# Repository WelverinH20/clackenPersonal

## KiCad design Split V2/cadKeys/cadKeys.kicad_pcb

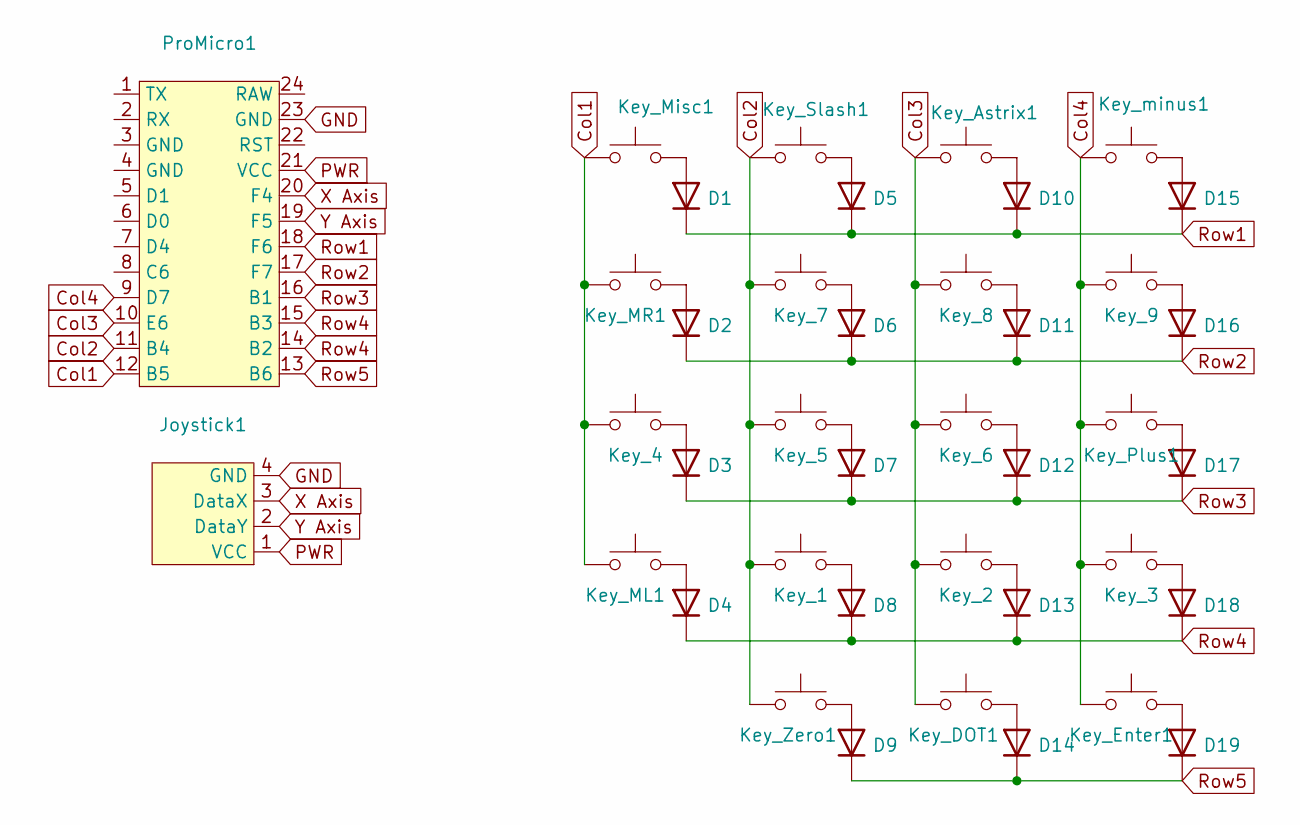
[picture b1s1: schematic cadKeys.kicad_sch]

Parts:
D1, D2, D3, D4, D5, D6, D7, D8, D9, D10, D11, D12, D13, D14, D15, D16, D17, D18, D19: D; D_SOD-123
Joystick1: joystick
Key_1, Key_2, Key_3, Key_4, Key_5, Key_6, Key_7, Key_8, Key_9: SW_Push; SW_Hotswap_Kailh_Choc_V1V2_1.00u
Key_Astrix1: SW_Push; SW_Hotswap_Kailh_Choc_V1V2_1.00u
Key_DOT1: SW_Push; SW_Hotswap_Kailh_Choc_V1V2_1.00u
Key_Enter1: SW_Push; SW_Hotswap_Kailh_Choc_V1V2_2.00u
Key_ML1: SW_Push; SW_Hotswap_Kailh_Choc_V1V2_1.00u
Key_MR1: SW_Push; SW_Hotswap_Kailh_Choc_V1V2_1.00u
Key_Misc1: SW_Push; SW_Hotswap_Kailh_Choc_V1V2_1.00u
Key_Plus1: SW_Push; SW_Hotswap_Kailh_Choc_V1V2_2.00u
Key_Slash1: SW_Push; SW_Hotswap_Kailh_Choc_V1V2_1.00u
Key_Zero1: SW_Push; SW_Hotswap_Kailh_Choc_V1V2_2.00u
Key_minus1: SW_Push; SW_Hotswap_Kailh_Choc_V1V2_1.00u
ProMicro1: ARDUINO_PRO_MICRO

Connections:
Col1: Key_4.1, Key_ML1.1, Key_MR1.1, Key_Misc1.1, ProMicro1.12 (B5)
Col2: Key_1.1, Key_5.1, Key_7.1, Key_Slash1.1, Key_Zero1.1, ProMicro1.11 (B4)
Col3: Key_2.1, Key_6.1, Key_8.1, Key_Astrix1.1, Key_DOT1.1, ProMicro1.10 (E6)
Col4: Key_3.1, Key_9.1, Key_Enter1.1, Key_Plus1.1, Key_minus1.1, ProMicro1.9 (D7)
GND: Joystick1.4 (GND), ProMicro1.23 (GND)
unnamed: D1.2 (A), Key_Misc1.2
unnamed: D2.2 (A), Key_MR1.2
unnamed: D3.2 (A), Key_4.2
unnamed: D4.2 (A), Key_ML1.2
unnamed: D5.2 (A), Key_Slash1.2
unnamed: D6.2 (A), Key_7.2
unnamed: D7.2 (A), Key_5.2
unnamed: D8.2 (A), Key_1.2
unnamed: D9.2 (A), Key_Zero1.2
unnamed: D10.2 (A), Key_Astrix1.2
unnamed: D11.2 (A), Key_8.2
unnamed: D12.2 (A), Key_6.2
unnamed: D13.2 (A), Key_2.2
unnamed: D14.2 (A), Key_DOT1.2
unnamed: D15.2 (A), Key_minus1.2
unnamed: D16.2 (A), Key_9.2
unnamed: D17.2 (A), Key_Plus1.2
unnamed: D18.2 (A), Key_3.2
unnamed: D19.2 (A), Key_Enter1.2
PWR: Joystick1.1 (VCC), ProMicro1.21 (VCC)
Row1: D1.1 (K), D5.1 (K), D10.1 (K), D15.1 (K), ProMicro1.18 (F6)
Row2: D2.1 (K), D6.1 (K), D11.1 (K), D16.1 (K), ProMicro1.17 (F7)
Row3: D3.1 (K), D7.1 (K), D12.1 (K), D17.1 (K), ProMicro1.16 (B1)
Row4: D4.1 (K), D8.1 (K), D13.1 (K), D18.1 (K), ProMicro1.14 (B2), ProMicro1.15 (B3)
Row5: D9.1 (K), D14.1 (K), D19.1 (K), ProMicro1.13 (B6)
X Axis: Joystick1.3 (DataX), ProMicro1.20 (F4)
Y Axis: Joystick1.2 (DataY), ProMicro1.19 (F5)

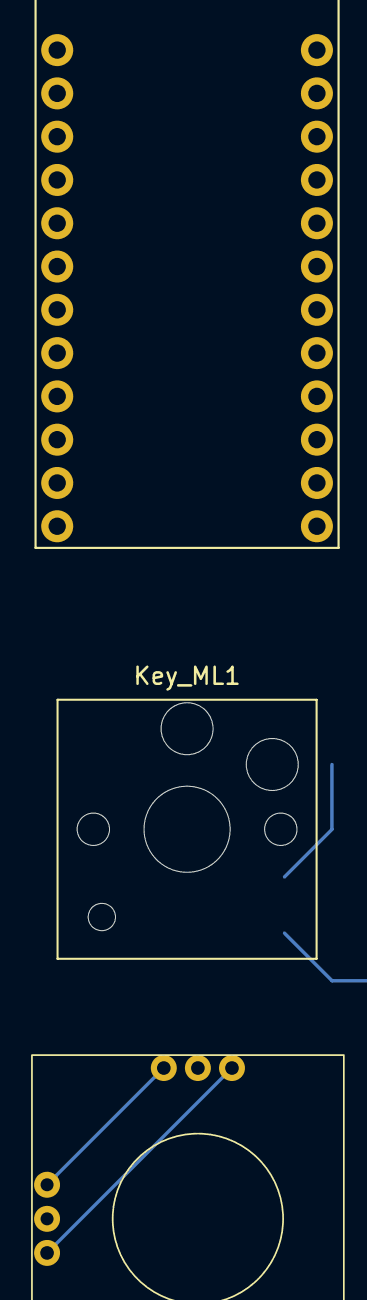
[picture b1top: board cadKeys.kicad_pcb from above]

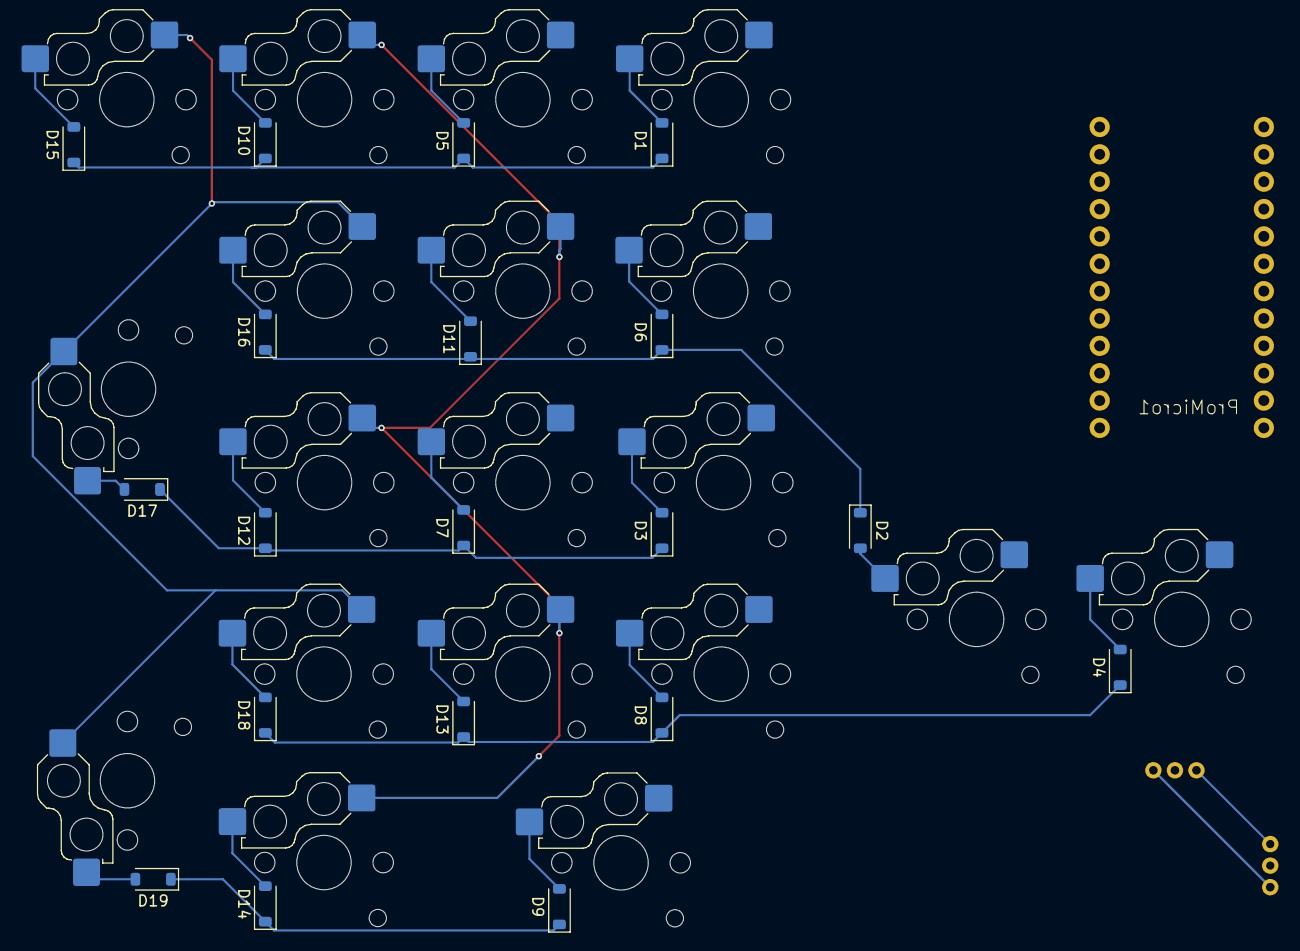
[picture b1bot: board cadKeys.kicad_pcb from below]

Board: 2 copper layers, 40 parts (19 on the bottom side), 32 nets.

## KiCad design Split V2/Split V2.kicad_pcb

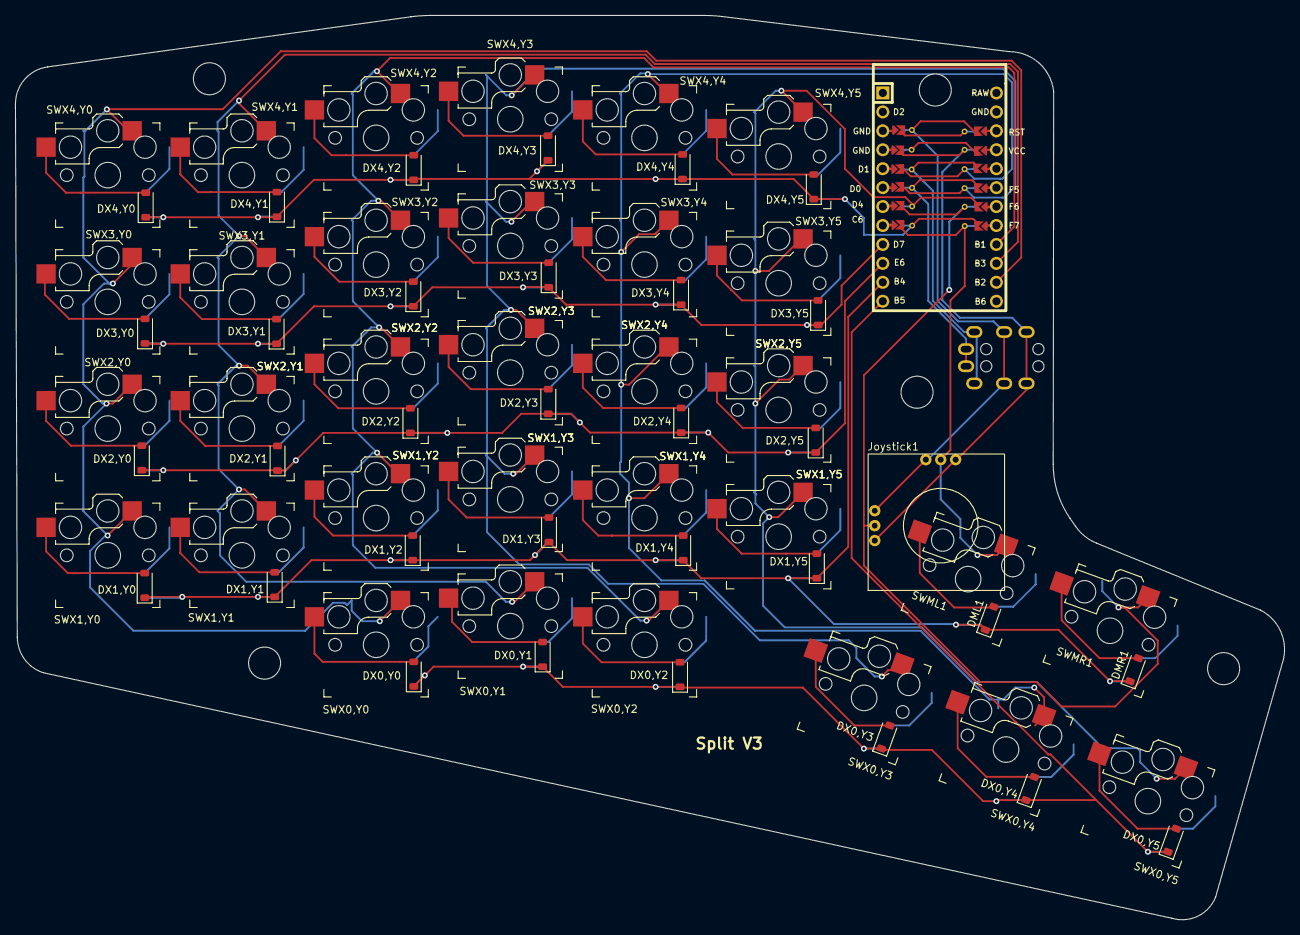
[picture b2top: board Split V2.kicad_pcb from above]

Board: 2 copper layers, 170.2 x 121.3 mm, 67 parts (0 on the bottom side), 49 nets.

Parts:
DML1: D_SOD-123_bothside
DMR1: D_SOD-123_bothside
DX0,Y0, DX0,Y1, DX0,Y2, DX0,Y3, DX0,Y4, DX0,Y5, DX1,Y0, DX1,Y1, DX1,Y2, DX1,Y3, DX1,Y4, DX1,Y5, DX2,Y0, DX2,Y1, DX2,Y2, DX2,Y3, DX2,Y4, DX2,Y5, DX3,Y0, DX3,Y1, DX3,Y2, DX3,Y3, DX3,Y4, DX3,Y5, DX4,Y0, DX4,Y1, DX4,Y2, DX4,Y3, DX4,Y4, DX4,Y5: D_SOD-123_bothside
J1: AudioJack4; TRRS-PJ-320A-dual
Joystick1: joystick
ProMicro1: ArduinoProMicro
SWML1: Kailh_socket_PG1350_optional_reversible
SWMR1: Kailh_socket_PG1350_optional_reversible
SWX0,Y0, SWX0,Y1, SWX0,Y2, SWX0,Y3, SWX0,Y4, SWX0,Y5, SWX1,Y0, SWX1,Y1, SWX1,Y2, SWX1,Y3, SWX1,Y4, SWX1,Y5, SWX2,Y0, SWX2,Y1, SWX2,Y2, SWX2,Y3, SWX2,Y4, SWX2,Y5, SWX3,Y0, SWX3,Y1, SWX3,Y2, SWX3,Y3, SWX3,Y4, SWX3,Y5, SWX4,Y0, SWX4,Y1, SWX4,Y2, SWX4,Y3, SWX4,Y4, SWX4,Y5: Kailh_socket_PG1350_optional_reversible

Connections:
/Net-(DX0,Y3-A): DML1.2 (A), SWML1.2
/Net-(DX0,Y4-A): DMR1.2 (A), SWMR1.2
Col0: ProMicro1.14 (B2), SWX0,Y0.1, SWX1,Y0.1, SWX2,Y0.1, SWX3,Y0.1, SWX4,Y0.1
Col1: ProMicro1.15 (B3), SWX0,Y1.1, SWX1,Y1.1, SWX2,Y1.1, SWX3,Y1.1, SWX4,Y1.1
Col2: ProMicro1.16 (B1), SWX0,Y2.1, SWX1,Y2.1, SWX2,Y2.1, SWX3,Y2.1, SWX4,Y2.1
Col3: ProMicro1.19 (F5), SWX0,Y3.1, SWX1,Y3.1, SWX2,Y3.1, SWX3,Y3.1, SWX4,Y3.1
Col4: ProMicro1.20 (F4), SWX0,Y4.1, SWX1,Y4.1, SWX2,Y4.1, SWX3,Y4.1, SWX4,Y4.1
Col5: ProMicro1.7 (D4), SWX0,Y5.1, SWX1,Y5.1, SWX2,Y5.1, SWX3,Y5.1, SWX4,Y5.1
Gnd: J1.3, Joystick1.4 (GND), ProMicro1.3 (GND)
Joy1: Joystick1.2 (DataY), ProMicro1.18 (F6), SWMR1.1
Joy2: Joystick1.3 (DataX), ProMicro1.17 (F7), SWML1.1
unnamed: DX0,Y0.2 (A), SWX0,Y0.2
unnamed: DX0,Y1.2 (A), SWX0,Y1.2
unnamed: DX0,Y2.2 (A), SWX0,Y2.2
unnamed: DX0,Y3.2 (A), SWX0,Y3.2
unnamed: DX0,Y4.2 (A), SWX0,Y4.2
unnamed: DX0,Y5.2 (A), SWX0,Y5.2
unnamed: DX1,Y0.2 (A), SWX1,Y0.2
unnamed: DX1,Y1.2 (A), SWX1,Y1.2
unnamed: DX1,Y2.2 (A), SWX1,Y2.2
unnamed: DX1,Y3.2 (A), SWX1,Y3.2
unnamed: DX1,Y4.2 (A), SWX1,Y4.2
unnamed: DX1,Y5.2 (A), SWX1,Y5.2
unnamed: DX2,Y0.2 (A), SWX2,Y0.2
unnamed: DX2,Y1.2 (A), SWX2,Y1.2
unnamed: DX2,Y2.2 (A), SWX2,Y2.2
unnamed: DX2,Y3.2 (A), SWX2,Y3.2
unnamed: DX2,Y4.2 (A), SWX2,Y4.2
unnamed: DX2,Y5.2 (A), SWX2,Y5.2
unnamed: DX3,Y0.2 (A), SWX3,Y0.2
unnamed: DX3,Y1.2 (A), SWX3,Y1.2
unnamed: DX3,Y2.2 (A), SWX3,Y2.2
unnamed: DX3,Y3.2 (A), SWX3,Y3.2
unnamed: DX3,Y4.2 (A), SWX3,Y4.2
unnamed: DX3,Y5.2 (A), SWX3,Y5.2
unnamed: DX4,Y0.2 (A), SWX4,Y0.2
unnamed: DX4,Y1.2 (A), SWX4,Y1.2
unnamed: DX4,Y2.2 (A), SWX4,Y2.2
unnamed: DX4,Y3.2 (A), SWX4,Y3.2
unnamed: DX4,Y4.2 (A), SWX4,Y4.2
unnamed: DX4,Y5.2 (A), SWX4,Y5.2
Row0: DX0,Y0.1 (K), DX0,Y1.1 (K), DX0,Y2.1 (K), DX0,Y3.1 (K), DX0,Y4.1 (K), DX0,Y5.1 (K), ProMicro1.12 (B5)
Row1: DML1.1 (K), DMR1.1 (K), DX1,Y0.1 (K), DX1,Y1.1 (K), DX1,Y2.1 (K), DX1,Y3.1 (K), DX1,Y4.1 (K), DX1,Y5.1 (K), ProMicro1.11 (B4)
Row2: DX2,Y0.1 (K), DX2,Y1.1 (K), DX2,Y2.1 (K), DX2,Y3.1 (K), DX2,Y4.1 (K), DX2,Y5.1 (K), ProMicro1.10 (E6)
Row3: DX3,Y0.1 (K), DX3,Y1.1 (K), DX3,Y2.1 (K), DX3,Y3.1 (K), DX3,Y4.1 (K), DX3,Y5.1 (K), ProMicro1.9 (D7)
Row4: DX4,Y0.1 (K), DX4,Y1.1 (K), DX4,Y2.1 (K), DX4,Y3.1 (K), DX4,Y4.1 (K), DX4,Y5.1 (K), ProMicro1.8 (C6)
SCL: J1.1, ProMicro1.6 (D0)
SDA: J1.2, ProMicro1.5 (D1)
VCC: J1.4, Joystick1.1 (VCC), ProMicro1.21 (VCC)

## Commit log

2024-11-23 Started fresh on a new split Kb
2024-11-23 Started on the PCB
    Created the Kicad Project file, pulled the PCB from ergogen. Started modifying the board and prepping for Schematic integration. Created a dual sided diode mount
2024-11-23 Connected schematic and pcb
    Got the Schematic and pcb linked and started searching for symbols for arduio promicro
2024-11-25 Did lots of stuff
    schematic, new symbols, footprint and such
2024-11-26 V1 Traces
    Got all of my traces layed out and worked on creating the reversable footprint like in other projects. Need to do some more research as to the specifics
2024-11-26 worked on making promicro revers
2024-11-26 Finished up double sided promicro
2024-11-26 Mounting
    Added mounting
2024-11-27 i did stuff
2024-11-27 updating
2024-12-04 adjusted mounting
2024-12-04 Cleaned up Silkscreen
2024-12-06 silkscreen work
2024-12-06 moved ttrs outlet
    not close enough to board edge
2024-12-09 Final adjustments made
    sent Gerber and drill files to jrcpcb
2024-12-30 Modified Split and made new
    Modified the original split to correct ADC error for joystick and started work on a Split keyboard with cherry switches
2025-03-27 Started new keyboard
    Cad keyboard to companion with 3dconnexion mouse
2025-04-26 Joystick practice
    got a joystick to work as a pointing device
